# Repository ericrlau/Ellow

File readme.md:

## NOTE: Not complete, do not use as is. 

### ToDo - update silk screen labels. Check schematic. Update gerbers. 

### Design based largely on nrfmicro from: https://github.com/joric/nrfmicro

### m.2 stuff from here : git@github.com:antmicro/m2-pcie-adapter.git

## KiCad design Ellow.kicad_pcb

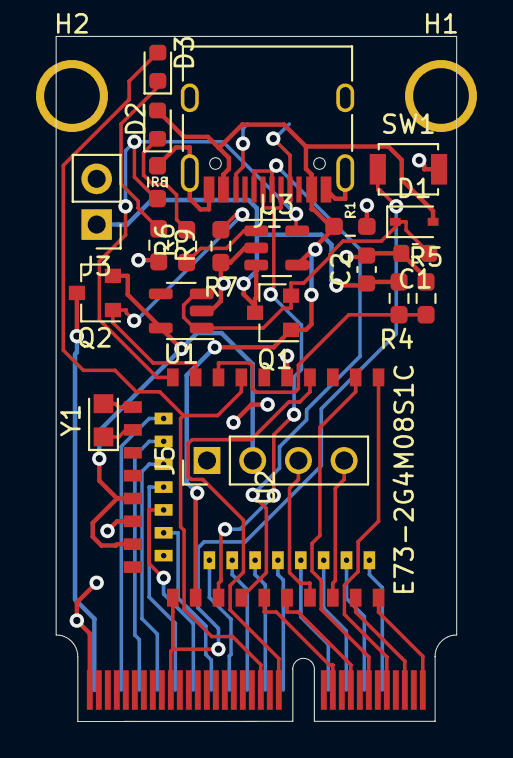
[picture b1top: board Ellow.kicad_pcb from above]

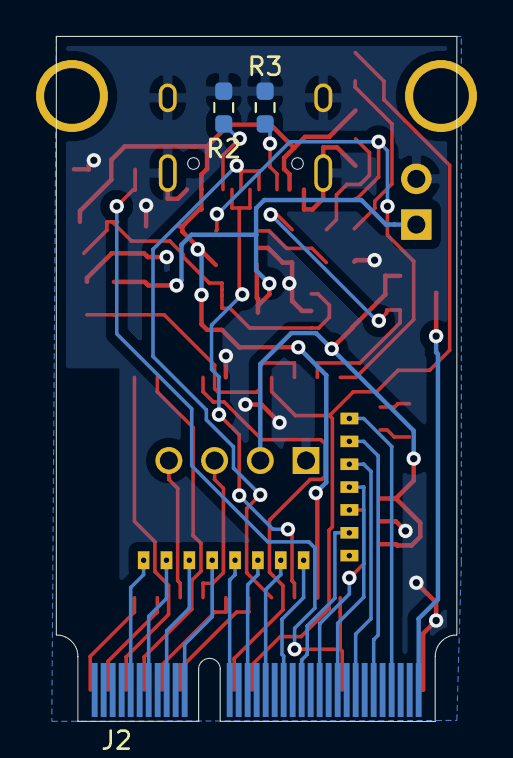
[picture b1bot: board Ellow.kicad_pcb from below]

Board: 2 copper layers, 22.2 x 38.1 mm, 27 parts (3 on the bottom side), 43 nets.

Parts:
C1, C2: 4.7uF; C_0603_1608Metric
D1: 1N5819; D_SOD-323
D2, D3: LED; LED_0603_1608Metric
H1, H2: MountingHole; MountingHole_M.2_3mm
J1: USB_C_Receptacle_USB2.0; USB_C_Receptacle_HRO_TYPE-C-31-M-12
J2: 2199119-4; M_2_EdgeConnector_E_Key
J3: Conn_01x02_Female; PinHeader_1x02_P2.54mm_Vertical
J5: Conn_01x04_Female; PinHeader_1x04_P2.54mm_Vertical_small
Q1, Q2: A03407; SOT-23
R1: 100k; R_0603_1608Metric_Pad0.98x0.95mm_HandSolder
R2, R3: 5.1k; R_0603_1608Metric_Pad0.98x0.95mm_HandSolder
R4: 820k; R_0603_1608Metric_Pad0.98x0.95mm_HandSolder
R5, R7: 2M; R_0603_1608Metric_Pad0.98x0.95mm_HandSolder
R6, R8, R9: 10k; R_0603_1608Metric_Pad0.98x0.95mm_HandSolder
SW1: SW_Push; SW_SPST_B3U-1000P
U1: AP2112K-3.3; SOT-23-5
U2: E73-2G4M08S1C; E73-2G4M08S1C-52840
U3: LN2054Y42AMR; SOT-23-5
Y1: 32.768kHz; Crystal_SMD_2012-2Pin_2.0x1.2mm_HandSoldering

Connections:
BATTERY_MEASURE: R4.2, R5.1, U2.8
DATA+: J1.A6, J1.B6, U2.31
DATA-: J1.A7, J1.B7, U2.29
EXT_VCC: J2.74, Q2.3
EXT_VCC_CONTROL: Q2.1, R7.1, U2.9
GND: C1.2, C2.2, J1.A1, J1.A12, J1.B1, J1.B12, J1.S1, J2.75, J3.2, J5.1, R1.2, R2.2, R3.2, R5.2, R7.2, R8.2, R9.2, SW1.2, U1.2, U2.5, U2.21, U2.24, U3.2
unnamed: C1.1, D1.1, Q1.2, U1.1, U1.3
unnamed: D2.1, R6.1
unnamed: D3.1, R9.1
unnamed: J1.A5, R2.1
unnamed: J1.B5, R3.1
unnamed: R6.2, U3.1
unnamed: U2.11, Y1.2
unnamed: U2.13, Y1.1
P0.02: D3.2, J2.37, U2.7
P0.04: J2.56, U2.18
P0.06: J2.64, U2.14
P0.07: J2.48, U2.22
P0.08: J2.60, U2.16
P0.09: J2.5, U2.41
P0.10: J2.1, U2.43
P0.12: J2.52, U2.20
P0.13: J2.21, U2.33
P0.15: J2.44, U2.28
P0.17: J2.40, U2.30
P0.20: J2.36, U2.32
P0.22: J2.32, U2.34
P0.24: J2.17, U2.35
P0.26: J2.68, U2.12
P0.28: J2.33, U2.4
P1.00: J2.22, U2.36
P1.02: J2.18, U2.38
P1.04: J2.14, U2.40
P1.06: J2.10, U2.42
P1.10: J2.13, U2.2
P1.11: J2.9, U2.1
PROG: R8.1, U2.10, U3.5
RESET: J2.57, SW1.1, U2.26
SWC: J5.4, U2.39
SWD: J5.3, U2.37
VBAT: C2.1, J3.1, Q1.3, R4.1, U3.3
VBUS: D1.2, D2.2, J1.A4, J1.A9, J1.B4, J1.B9, Q1.1, R1.1, U2.27, U3.4
VDD_H: J5.2, Q2.2, U1.5, U2.19, U2.23

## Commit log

2020-11-15 schematic started
2020-11-19 more updates, not complete
2020-11-20 schematic getting close to ready for pcb start
2020-11-20 first parts associated with footprints on pcb
2020-11-21 initial m_2 stuff
2020-11-21 saved
2020-11-21 moved shield stuff to another board
2020-11-21 first board for quote check. not routed
2020-11-22 starting to look at routing
2020-11-22 no routing solution yet
2020-11-23 prelim routing
2020-11-24 routing done, R0
2020-11-27 first autoroute attempt
2020-12-06 routed and ready for QA check
2020-12-06 minor updates, notes
